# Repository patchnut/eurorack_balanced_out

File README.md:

# Eurorack Balanced Out
Stereo balanced output board with attenuation for in eurorack cases.

This is a Kicad project for a balanced output board to build in the back of an Eurorack case. This is not a eurorack
module, but instead can be built into a eurorack case to provide two balanced outputs on TRS jacks on the back of the case.
The circuit is powered from a normal +12v/-12v eurorack power supply and can be connected to a module that provides
mini-jack connectors so signals can be patched into the output. The current assumption is that we can use the Doepfer A-139-2 
Headphone Amplifier module for this. It provides mini jack inputs, volume control and has two un-populated headers on the board
that look like they provide outputs.

Features
- Two balanced 6,3 mm TRS jack outputs
- 10 pin eurorack compatible power connector for +12v/-12v
- 1/4 attenuation, use different resistors to change attenuation level
- two THAT1646 output drivers
- inputs on two 2-pin headers for internal connection to front panel module

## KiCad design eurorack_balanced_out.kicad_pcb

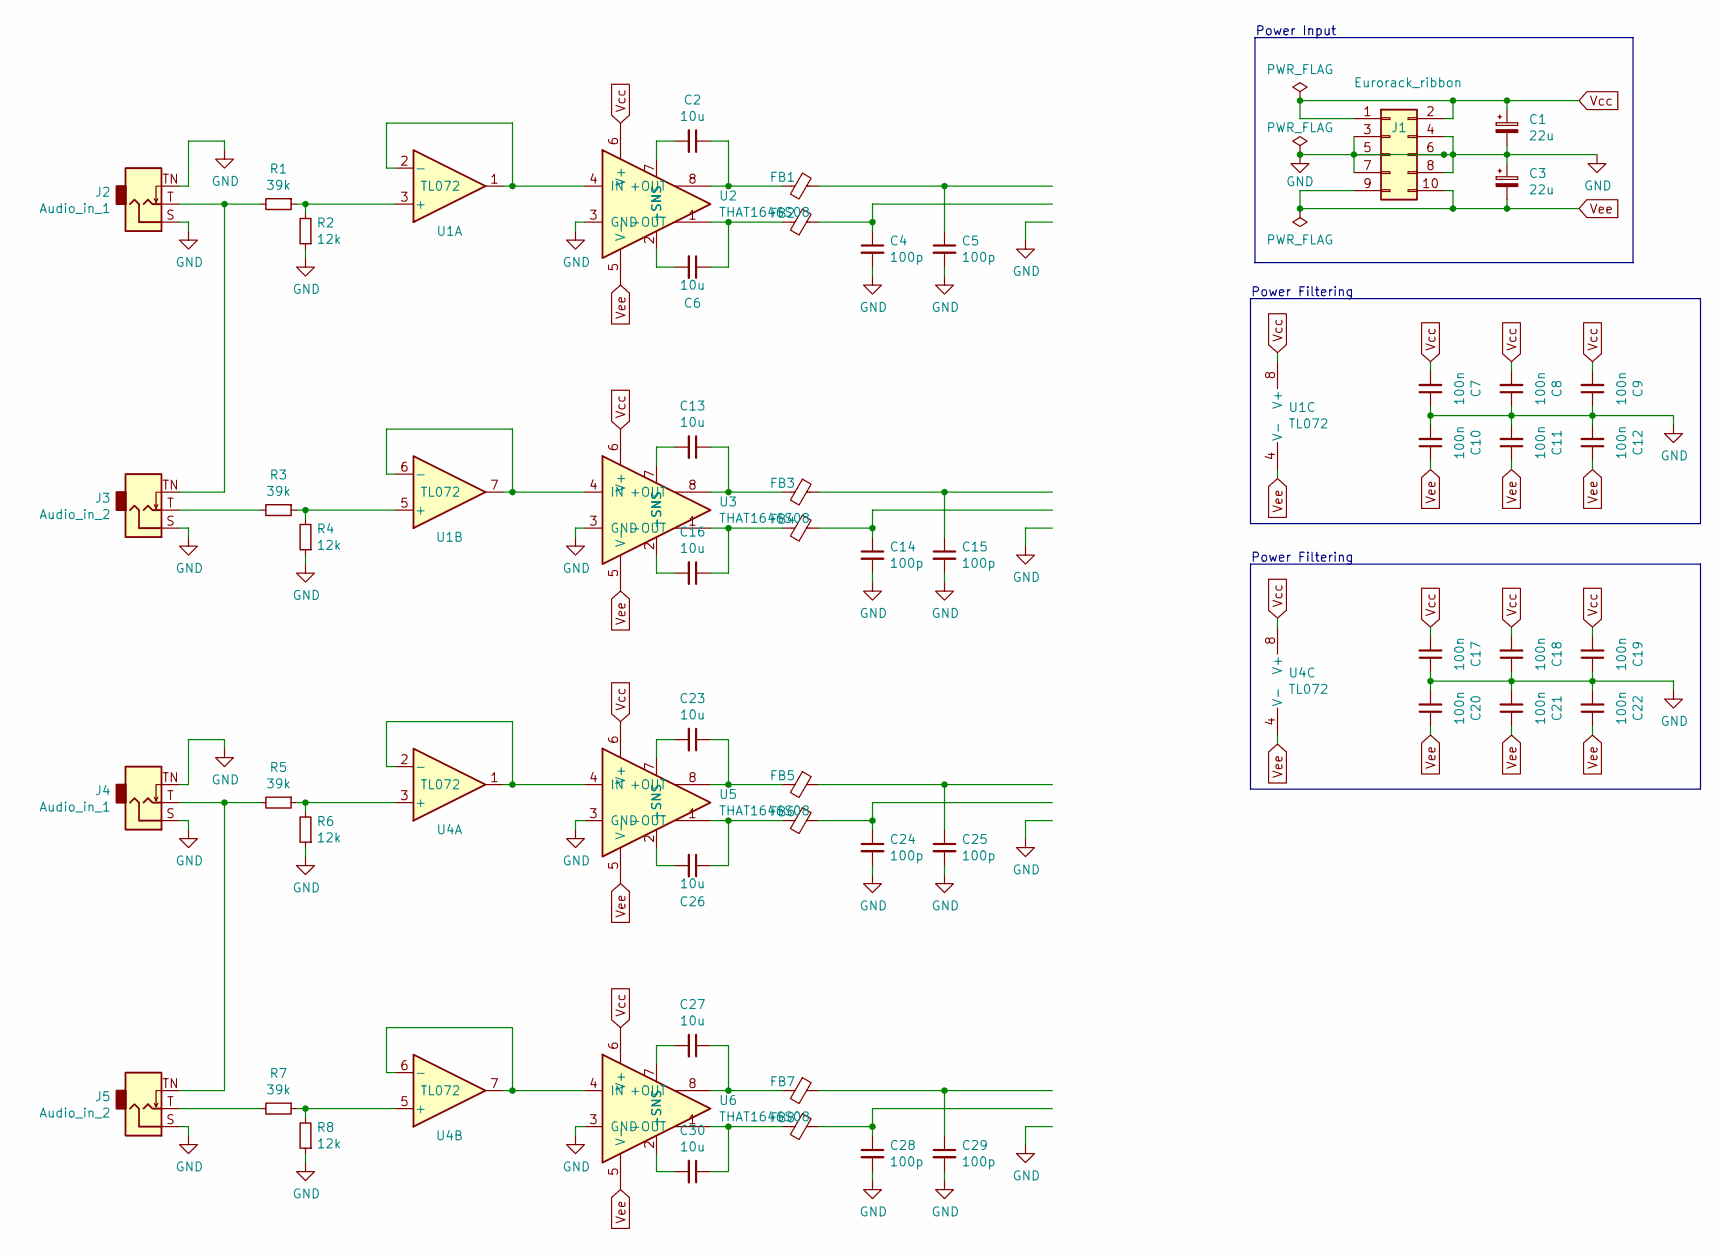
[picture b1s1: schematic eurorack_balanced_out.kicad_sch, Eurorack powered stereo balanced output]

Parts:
C1, C3: 22u; CP_Elec_6.3x5.4; Mouser 647-UWT1E220MCL1B
C2, C6, C13, C16, C23, C26, C27, C30: 10u; CP_Elec_6.3x5.4; Mouser 647-UWP1E100MCL
C4, C5, C14, C15, C24, C25, C28, C29: 100p; C_0805_2012Metric_Pad1.18x1.45mm_HandSolder; Mouser 80-C0805C101JAGAUTO
C7, C8, C9, C10, C11, C12, C17, C18, C19, C20, C21, C22: 100n; C_0805_2012Metric_Pad1.18x1.45mm_HandSolder; Mouser 80-C0805C104K5RACLR
FB1, FB2, FB3, FB4, FB5, FB6, FB7, FB8: 600R @ 100Mhz; R_0805_2012Metric_Pad1.20x1.40mm_HandSolder; Mouser 81-BLM21A601F
J1: Eurorack_ribbon; PinHeader_2x05_P2.54mm_Vertical; Mouser 200-TSS10501TD
J2, J4: Audio_in_1; Jack_3.5mm_QingPu_WQP-PJ398SM_Vertical_CircularHoles
J3, J5: Audio_in_2; Jack_3.5mm_QingPu_WQP-PJ398SM_Vertical_CircularHoles
R1, R3, R5, R7: 39k; R_0805_2012Metric_Pad1.20x1.40mm_HandSolder; Mouser 667-ERJ-6ENF3901V
R2, R4, R6, R8: 12k; R_0805_2012Metric_Pad1.20x1.40mm_HandSolder; Mouser 667-ERJ-S06F1201V
U1, U4: TL072; SO-8_5.3x6.2mm_P1.27mm
U2, U3, U5, U6: THAT1646S08; SOIC-8_3.9x4.9mm_P1.27mm

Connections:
GND: C1.2, C3.1, C4.2, C5.2, C7.1, C8.1, C9.1, C10.2, C11.2, C12.2, C14.2, C15.2, C17.1, C18.1, C19.1, C20.2, C21.2, C22.2, C24.2, C25.2, C28.2, C29.2, J1.3, J1.4, J1.5, J1.6, J1.7, J1.8, J2.S, J2.TN, J3.S, J4.S, J4.TN, J5.S, R2.1, R4.1, R6.1, R8.1, U2.3 (GND), U3.3 (GND), U5.3 (GND), U6.3 (GND)
unnamed: C4.1, FB2.1
unnamed: C5.1, FB1.1
unnamed: C14.1, FB4.1
unnamed: C15.1, FB3.1
unnamed: C24.1, FB6.1
unnamed: C25.1, FB5.1
unnamed: C28.1, FB8.1
unnamed: C29.1, FB7.1
unnamed: J2.T, J3.TN, R1.2
unnamed: J3.T, R3.2
unnamed: J4.T, J5.TN, R5.2
unnamed: J5.T, R7.2
unnamed: R1.1, R2.2, U1.3 (+)
unnamed: U1.1, U1.2 (-), U2.4 (IN)
unnamed: R3.1, R4.2, U1.5 (+)
unnamed: U1.6 (-), U1.7, U3.4 (IN)
unnamed: C2.1, FB1.2, U2.8 (+OUT)
unnamed: C2.2, U2.7 (+SNS)
unnamed: C6.1, FB2.2, U2.1 (-OUT)
unnamed: C6.2, U2.2 (-SNS)
unnamed: C13.1, FB3.2, U3.8 (+OUT)
unnamed: C13.2, U3.7 (+SNS)
unnamed: C16.1, FB4.2, U3.1 (-OUT)
unnamed: C16.2, U3.2 (-SNS)
unnamed: R5.1, R6.2, U4.3 (+)
unnamed: U4.1, U4.2 (-), U5.4 (IN)
unnamed: R7.1, R8.2, U4.5 (+)
unnamed: U4.6 (-), U4.7, U6.4 (IN)
unnamed: C23.1, FB5.2, U5.8 (+OUT)
unnamed: C23.2, U5.7 (+SNS)
unnamed: C26.1, FB6.2, U5.1 (-OUT)
unnamed: C26.2, U5.2 (-SNS)
unnamed: C27.1, FB7.2, U6.8 (+OUT)
unnamed: C27.2, U6.7 (+SNS)
unnamed: C30.1, FB8.2, U6.1 (-OUT)
unnamed: C30.2, U6.2 (-SNS)
Vcc: C1.1, C7.2, C8.2, C9.2, C17.2, C18.2, C19.2, J1.1, J1.2, U1.8 (V+), U2.6 (V+), U3.6 (V+), U4.8 (V+), U5.6 (V+), U6.6 (V+)
Vee: C3.2, C10.1, C11.1, C12.1, C20.1, C21.1, C22.1, J1.9, J1.10, U1.4 (V-), U2.5 (V-), U3.5 (V-), U4.4 (V-), U5.5 (V-), U6.5 (V-)

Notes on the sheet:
Power Filtering
Power Input

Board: 2 copper layers, 57 parts (0 on the bottom side), 39 nets, no tracks yet.

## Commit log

2020-05-14 init project
2020-05-21 add output drivers for both channels
2020-05-21 add eurorack power connector + filtering
2020-05-21 add input connectors
2020-05-21 add output jacks
2020-05-21 use new that 1646 component
2020-05-22 add output footprint
2020-05-22 delete a channel
    we'll duplicate it again when we're done
2020-05-22 add output protection diodes
2020-05-22 output emc filtering
2020-05-22 re-add second channel
2020-05-22 annotate components
2020-05-22 fix erc errors
2020-05-23 replace 1n4004 output protection diodes with BAV99
2020-05-23 replace resistor symbols with R small
2020-05-23 replace capacitors with small versions
2020-05-23 add pinheader footprints
2020-05-23 fix protection diode orientation
2020-05-23 reannotate
2020-05-23 fix weird erc non connected error
2020-05-24 fix power connector footprint
2020-05-24 start pcb layout
2020-05-24 rought first placement
2020-05-26 try to make placement a bit more compact
2020-05-26 save some more board space
2020-05-27 clean up component placement
2020-05-27 clean up edgecut
2020-05-27 route signals and some power
2020-05-27 prepare for power routing and cleanup
2020-05-27 fix ground planes
2020-05-27 more cleanup
2020-05-27 left channel power routing
2020-05-28 rout rest of power
2020-05-28 small track cleanup
2020-05-28 fix silkscreen
2020-05-29 add some mouser part numbers
2020-05-29 fix some resistor values
2020-05-29 finish mouser part numbers
2020-05-29 use different footprint for 10uF cap so we can use the 25V version
2020-05-29 change mouser part number for 10u non polarized caps to 25v version
2020-05-30 set revision number in schematic
2020-05-30 set pcb page settins
2020-05-30 fix fills and edge cuts to new board size
2020-05-30 prepare room for decoupling caps
2020-05-30 fix decoupling caps in schematic
2020-05-31 fixed lost piece of silkscreen text
2020-05-31 fix missing connections
2020-05-31 place decoupling caps
2020-05-31 optimize channel input placement
2020-05-31 removed plus from non-polarized elco footprints
2020-05-31 fix silkscreen so it doesnt change back again
2020-05-31 route signals
2020-05-31 finish routing
2020-05-31 edgecut rounded corners
2020-05-31 re-fill before export and ordering
2020-06-05 add revision to silkscreen
2020-06-06 gitignore plotted gerbers
2020-06-11 define track with for power netclass
2020-06-11 rotate power connector and capacitors
2020-06-11 fix silkscreen for power connector orientation
2020-06-11 re-route power (again)
2020-06-11 rotated input capacitors to improve ground continuity
2020-06-26 add measurements
2020-07-07 revision 0.1.1
2021-04-29 update schematic, add input buffer
2021-04-29 increase input impedance
2021-04-29 set input and output jacks
2021-05-05 Cleanup of Schematic
    Separated input and output clamps
    Improved formatting
2021-05-09 fix typo in THAT1646 symbol reference
2021-05-09 use thonkycon TRS footprint for outputs
2021-05-09 add board outline and move components out of the way
2021-05-09 roughly place components
2021-05-09 flip chips to back of the board
2021-05-09 add ground planes
2021-05-09 fix connector placement
2021-05-09 rough place output filtering
2021-05-09 group power filtering caps with chips
2021-05-11 route some stuff
2021-05-12 remove clamps from schematic
2021-05-12 re-layout pcb make room for power header layout the board so left->right = top->bottom remove clamp diodes everything on one side
2023-04-03 make schematic 4 channel
    remove output jacks
    clean up layout
2023-10-01 update buffer to ne5532
